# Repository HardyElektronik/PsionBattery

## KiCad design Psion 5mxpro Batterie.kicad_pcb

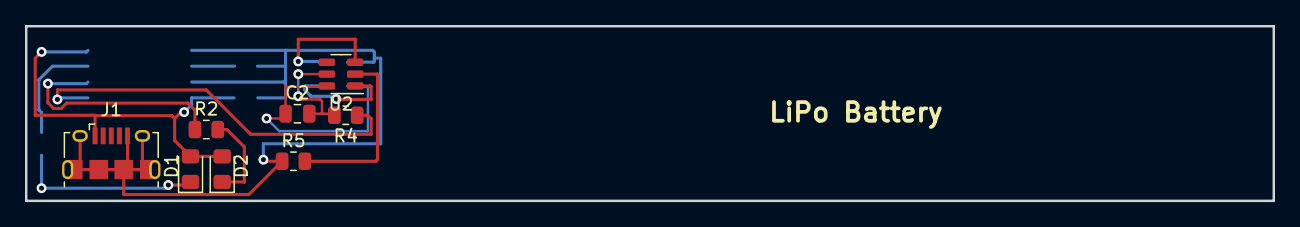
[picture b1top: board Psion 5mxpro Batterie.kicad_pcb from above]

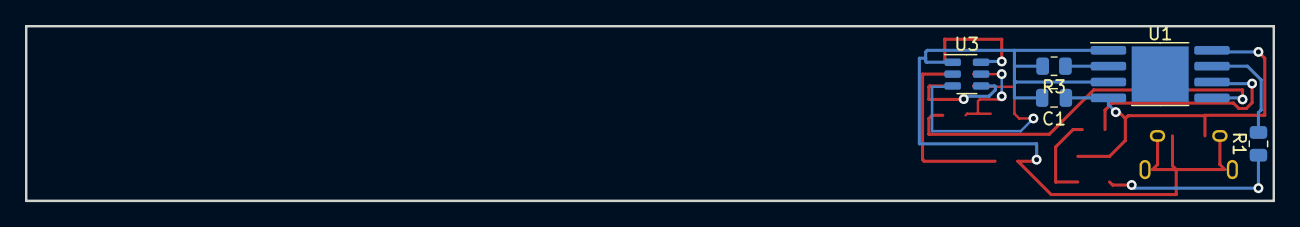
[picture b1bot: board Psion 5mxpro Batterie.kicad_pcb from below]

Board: 2 copper layers, 100.0 x 14.0 mm, 13 parts (5 on the bottom side), 13 nets.

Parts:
C?: C; C_0805_2012Metric
C?#2: 10µ; C_0805_2012Metric
D2: Green; LED_0805_2012Metric_Pad1.15x1.40mm_HandSolder
D?: Red; LED_0805_2012Metric_Pad1.15x1.40mm_HandSolder
J1: USB_B_Micro; USB_Micro-B_Amphenol_10118194_Horizontal
R2: 1k; R_0805_2012Metric
R3: 2k4; R_0805_2012Metric
R4: 100; R_0805_2012Metric
R5: 2k; R_0805_2012Metric
R?: 1k; R_0805_2012Metric
U?: FS312F-G; SOT-23-6
U?#2: FS8205; SOT-23-6
U?#3: TP4056; SOP-8-1EP_4.57x4.57mm_P1.27mm_EP4.57x4.45mm

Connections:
BAT+: C?.2, R4.2, U?.5 (VCC)
BAT-: C?.1, U?.6 (GND), U?#2.3 (S2)
GNDREF: C?#2.2, J1.5 (GND), J1.6 (Shield), R3.2, R5.1, U?#2.1 (S1), U?#3.1 (TEMP), U?#3.3 (GND)
unnamed: D?.1 (K), R?.2
unnamed: D2.1 (K), R2.2
unnamed: R?.1, U?#3.7 (CHRG)
unnamed: R2.1, U?#3.6 (STDBYY)
unnamed: R3.1, U?#3.2 (PROG)
unnamed: R4.1, U?#3.5 (BAT)
unnamed: R5.2, U?.2 (CS)
unnamed: U?.3 (OC), U?#2.6 (G1)
unnamed: U?.1 (OD), U?#2.4 (G2)
VBUS: C?#2.1, D2.2 (A), D?.2 (A), J1.1 (VBUS), U?#3.4 (VCC), U?#3.8 (CE)
